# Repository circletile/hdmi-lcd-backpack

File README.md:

# hdmi-lcd-backpack
An HDMI signal converter backpack PCB

A circuit I designed for my electrical/computer engineering senior design project. Takes up to 1080p HDMI video signals, feeds them to a TI TFP401A signal converter, and directly drives an attached LCD. Also provides capacitive touch sensing, backlight control, and DDC data.

A few months later a similar product appeared for sale on Adafruit (#2219). Much easier to just buy theirs than to try to hand solder the TFP401A under a microscope like I did...

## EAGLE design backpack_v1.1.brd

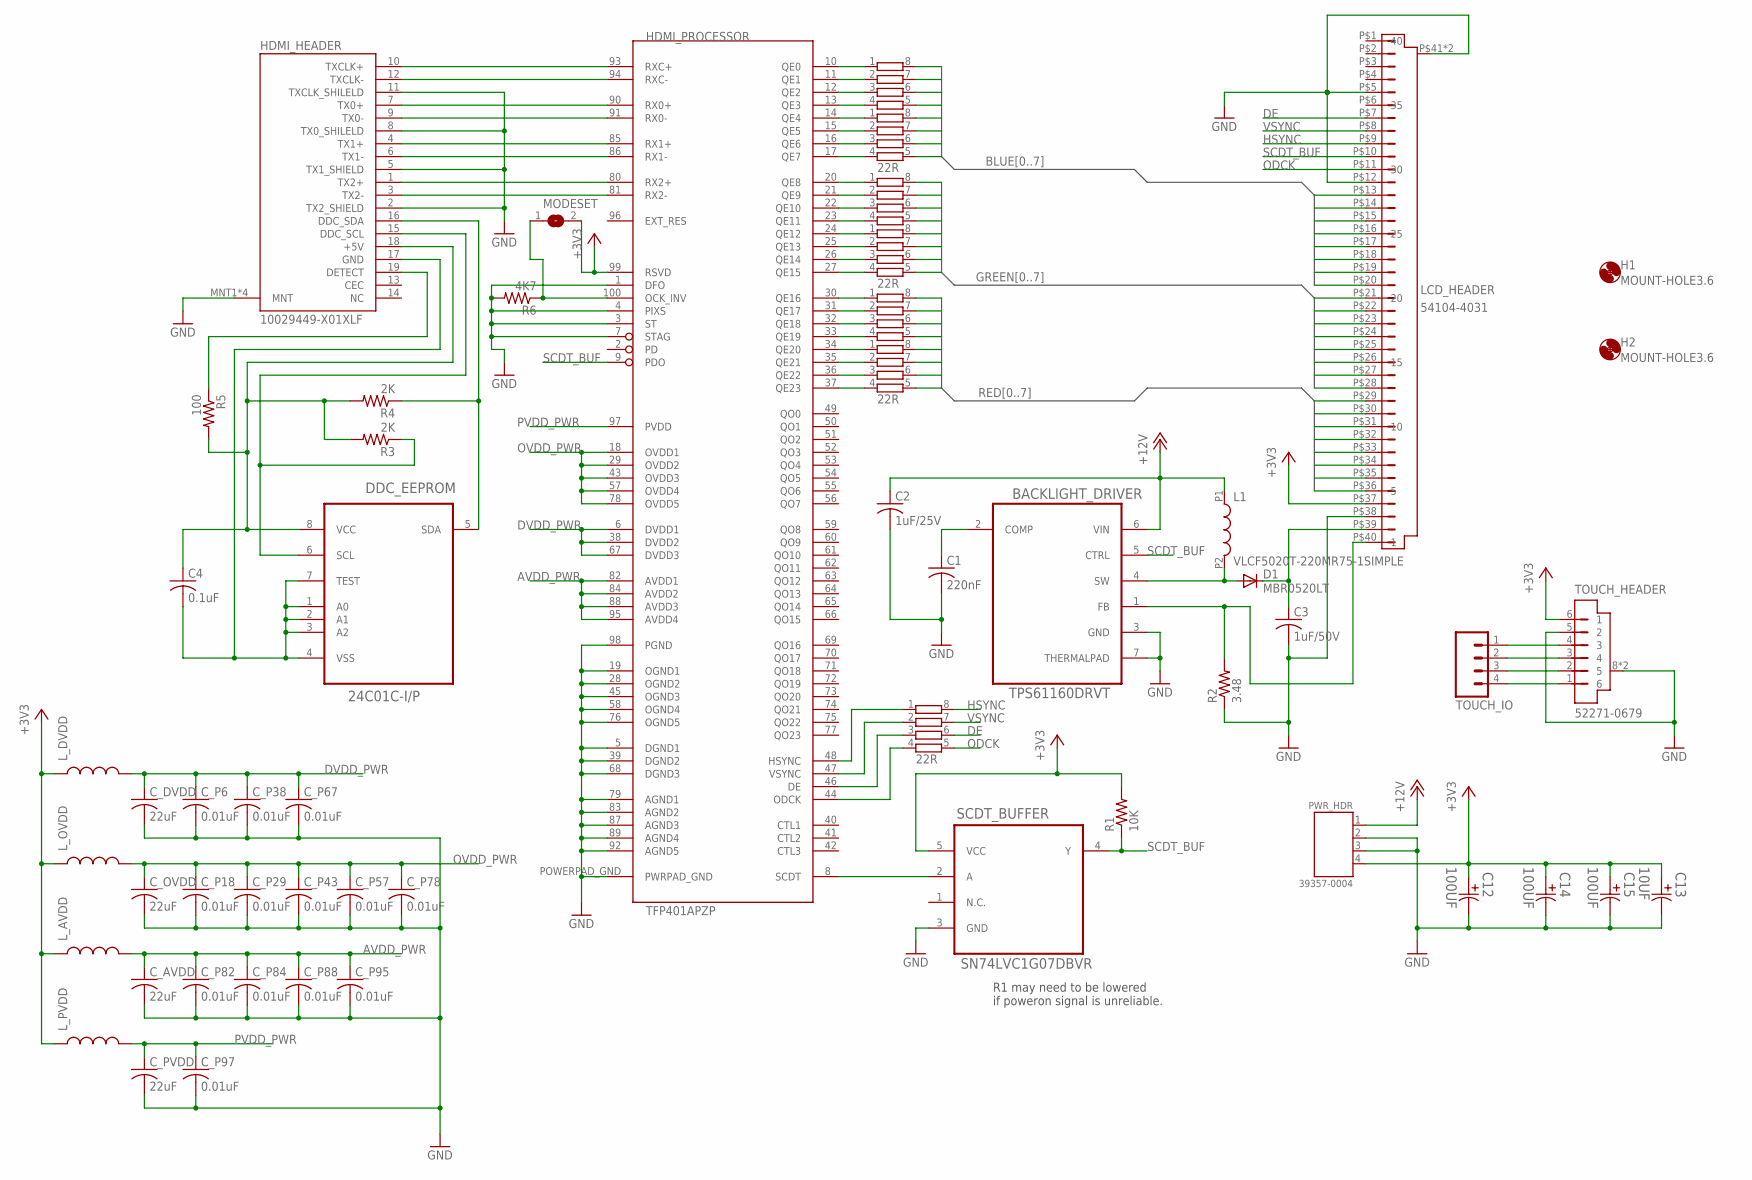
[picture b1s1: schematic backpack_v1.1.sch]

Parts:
BACKLIGHT_DRIVER: TPS61160DRVT; SON65P210X210X80-7N
C1: 220nF; C0805
C2: 1uF/25V; C0603
C3: 1uF/50V; C0805
C4: 0.1uF; C0603
C12, C14, C15: 100UF; CAPPR350-800X1150
C13: 10UF; CAPPR150-400X700
C_AVDD: 22uF; C0603
C_DVDD: 22uF; C0603
C_OVDD: 22uF; C0603
C_P6, C_P18, C_P29, C_P38, C_P43, C_P57, C_P67, C_P78, C_P82, C_P84, C_P88, C_P95, C_P97: 0.01uF; C0603
C_PVDD: 22uF; C0603
D1: MBR0520LT; SOD123
DDC_EEPROM: 24C01C-I/P; DIP254P762X533-8
H1, H2: MOUNT-HOLE3.6; 3,6
HDMI_HEADER: 10029449-X01XLF; 10029449
HDMI_PROCESSOR: TFP401APZP; 100-TQFP(PZP)
L1: VLCF5020T-220MR75-1SIMPLE; VLCF5020-1_SIMPLE
LCD_HEADER: 54104-4031
L_AVDD: INDUCTOR0603; 0603
L_DVDD: INDUCTOR0603; 0603
L_OVDD: INDUCTOR0603; 0603
L_PVDD: INDUCTOR0603; 0603
MODESET: SJ
PWR_HDR: 39357-0004
R1: 10K; R0805
R2: 3.48; R0805
R3, R4: 2K; R0805
R5: 100; R0805
R6: 4K7; R0805
RN1, RN2, RN3, RN4, RN5, RN6, RN7: 22R; CAY16
SCDT_BUFFER: SN74LVC1G07DBVR; SOT95P280X145-5N
TOUCH_HEADER: 52271-0679
TOUCH_IO: M04POLAR; MOLEX-1X4

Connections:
+3V3: C12.1, C13.1, C14.1, C15.1, HDMI_PROCESSOR.99 (RSVD), LCD_HEADER.P$37 (4), L_AVDD.1, L_DVDD.1, L_OVDD.1, L_PVDD.1, MODESET.2, PWR_HDR.4, R1.2, SCDT_BUFFER.5 (VCC), TOUCH_HEADER.6 (1)
+5V: C4.1, DDC_EEPROM.8 (VCC), HDMI_HEADER.18 (+5V), R3.2, R4.2, R5.2
+12V: BACKLIGHT_DRIVER.6 (VIN), C2.1, L1.P1, PWR_HDR.1
AVDD_PWR: C_AVDD.1, C_P82.1, C_P84.1, C_P88.1, C_P95.1, HDMI_PROCESSOR.82 (AVDD1), HDMI_PROCESSOR.84 (AVDD2), HDMI_PROCESSOR.88 (AVDD3), HDMI_PROCESSOR.95 (AVDD4), L_AVDD.2
BLUE0: LCD_HEADER.P$20 (21), RN1.8 (2)
BLUE1: LCD_HEADER.P$19 (22), RN1.7 (2)
BLUE2: LCD_HEADER.P$18 (23), RN1.6 (2)
BLUE3: LCD_HEADER.P$17 (24), RN1.5 (2)
BLUE4: LCD_HEADER.P$16 (25), RN2.8 (2)
BLUE5: LCD_HEADER.P$15 (26), RN2.7 (2)
BLUE6: LCD_HEADER.P$14 (27), RN2.6 (2)
BLUE7: LCD_HEADER.P$13 (28), RN2.5 (2)
DDC_SCL: DDC_EEPROM.6 (SCL), HDMI_HEADER.15 (DDC_SCL), R3.1
DDC_SDA: DDC_EEPROM.5 (SDA), HDMI_HEADER.16 (DDC_SDA), R4.1
DE: LCD_HEADER.P$7 (34), RN7.6 (2)
DVDD_PWR: C_DVDD.1, C_P6.1, C_P38.1, C_P67.1, HDMI_PROCESSOR.6 (DVDD1), HDMI_PROCESSOR.38 (DVDD2), HDMI_PROCESSOR.67 (DVDD3), L_DVDD.2
GND: BACKLIGHT_DRIVER.3 (GND), BACKLIGHT_DRIVER.7 (THERMALPAD), C1.2, C2.2, C3.2, C12.2, C13.2, C14.2, C15.2, C_AVDD.2, C_DVDD.2, C_OVDD.2, C_P6.2, C_P18.2, C_P29.2, C_P38.2, C_P43.2, C_P57.2, C_P67.2, C_P78.2, C_P82.2, C_P84.2, C_P88.2, C_P95.2, C_P97.2, C_PVDD.2, HDMI_HEADER.2 (TX2_SHIELD), HDMI_HEADER.5 (TX1_SHIELD), HDMI_HEADER.8 (TX0_SHILELD), HDMI_HEADER.11 (TXCLK_SHILELD), HDMI_HEADER.MNT1 (MNT), HDMI_HEADER.MNT2 (MNT), HDMI_HEADER.MNT3 (MNT), HDMI_HEADER.MNT4 (MNT), HDMI_PROCESSOR.1 (DFO), HDMI_PROCESSOR.3 (ST), HDMI_PROCESSOR.4 (PIXS), HDMI_PROCESSOR.5 (DGND1), HDMI_PROCESSOR.7 (STAG), HDMI_PROCESSOR.19 (OGND1), HDMI_PROCESSOR.28 (OGND2), HDMI_PROCESSOR.39 (DGND2), HDMI_PROCESSOR.45 (OGND3), HDMI_PROCESSOR.58 (OGND4), HDMI_PROCESSOR.68 (DGND3), HDMI_PROCESSOR.76 (OGND5), HDMI_PROCESSOR.79 (AGND1), HDMI_PROCESSOR.83 (AGND2), HDMI_PROCESSOR.87 (AGND3), HDMI_PROCESSOR.89 (AGND4), HDMI_PROCESSOR.92 (AGND5), HDMI_PROCESSOR.98 (PGND), HDMI_PROCESSOR.POWERPAD_GND (PWRPAD_GND), LCD_HEADER.P$5 (36), LCD_HEADER.P$12 (29), LCD_HEADER.P$38 (3), LCD_HEADER.P$41 (GND), LCD_HEADER.P$42 (GND), PWR_HDR.2, PWR_HDR.3, R2.1, R6.2, SCDT_BUFFER.3 (GND), TOUCH_HEADER.5 (2), TOUCH_HEADER.8 (GND), TOUCH_HEADER.9 (GND)
GREEN0: LCD_HEADER.P$28 (13), RN3.8 (2)
GREEN1: LCD_HEADER.P$27 (14), RN3.7 (2)
GREEN2: LCD_HEADER.P$26 (15), RN3.6 (2)
GREEN3: LCD_HEADER.P$25 (16), RN3.5 (2)
GREEN4: LCD_HEADER.P$24 (17), RN4.8 (2)
GREEN5: LCD_HEADER.P$23 (18), RN4.7 (2)
GREEN6: LCD_HEADER.P$22 (19), RN4.6 (2)
GREEN7: LCD_HEADER.P$21 (20), RN4.5 (2)
HDMI_DETECT: HDMI_HEADER.19 (DETECT), R5.1
HDMI_GND: C4.2, DDC_EEPROM.1 (A0), DDC_EEPROM.2 (A1), DDC_EEPROM.3 (A2), DDC_EEPROM.4 (VSS), DDC_EEPROM.7 (TEST), HDMI_HEADER.17 (GND)
HSYNC: LCD_HEADER.P$9 (32), RN7.8 (2)
unnamed: HDMI_PROCESSOR.10 (QE0), RN1.1
unnamed: HDMI_PROCESSOR.11 (QE1), RN1.2 (1)
unnamed: HDMI_PROCESSOR.12 (QE2), RN1.3 (1)
unnamed: HDMI_PROCESSOR.13 (QE3), RN1.4 (1)
unnamed: HDMI_PROCESSOR.14 (QE4), RN2.1
unnamed: HDMI_PROCESSOR.15 (QE5), RN2.2 (1)
unnamed: HDMI_PROCESSOR.16 (QE6), RN2.3 (1)
unnamed: HDMI_PROCESSOR.17 (QE7), RN2.4 (1)
unnamed: HDMI_PROCESSOR.20 (QE8), RN3.1
unnamed: HDMI_PROCESSOR.21 (QE9), RN3.2 (1)
unnamed: HDMI_PROCESSOR.22 (QE10), RN3.3 (1)
unnamed: HDMI_PROCESSOR.23 (QE11), RN3.4 (1)
unnamed: HDMI_PROCESSOR.24 (QE12), RN4.1
unnamed: HDMI_PROCESSOR.25 (QE13), RN4.2 (1)
unnamed: HDMI_PROCESSOR.26 (QE14), RN4.3 (1)
unnamed: HDMI_PROCESSOR.27 (QE15), RN4.4 (1)
unnamed: HDMI_PROCESSOR.30 (QE16), RN5.1
unnamed: HDMI_PROCESSOR.31 (QE17), RN5.2 (1)
unnamed: HDMI_PROCESSOR.32 (QE18), RN5.3 (1)
unnamed: HDMI_PROCESSOR.33 (QE19), RN5.4 (1)
unnamed: HDMI_PROCESSOR.34 (QE20), RN6.1
unnamed: HDMI_PROCESSOR.35 (QE21), RN6.2 (1)
unnamed: HDMI_PROCESSOR.36 (QE22), RN6.3 (1)
unnamed: HDMI_PROCESSOR.37 (QE23), RN6.4 (1)
unnamed: BACKLIGHT_DRIVER.4 (SW), D1.A, L1.P2
unnamed: BACKLIGHT_DRIVER.2 (COMP), C1.1
unnamed: BACKLIGHT_DRIVER.1 (FB), LCD_HEADER.P$40 (1), R2.2
unnamed: HDMI_PROCESSOR.44 (ODCK), RN7.4 (1)
unnamed: C3.1, D1.C, LCD_HEADER.P$39 (2)
unnamed: HDMI_PROCESSOR.46 (DE), RN7.3 (1)
unnamed: HDMI_PROCESSOR.47 (VSYNC), RN7.2 (1)
unnamed: HDMI_PROCESSOR.48 (HSYNC), RN7.1
unnamed: TOUCH_HEADER.4 (3), TOUCH_IO.1
unnamed: TOUCH_HEADER.3 (4), TOUCH_IO.2
unnamed: TOUCH_HEADER.2 (5), TOUCH_IO.3
unnamed: TOUCH_HEADER.1 (6), TOUCH_IO.4
OCK_INV: HDMI_PROCESSOR.100 (OCK_INV), MODESET.1, R6.1
ODCK: LCD_HEADER.P$11 (30), RN7.5 (2)
OVDD_PWR: C_OVDD.1, C_P18.1, C_P29.1, C_P43.1, C_P57.1, C_P78.1, HDMI_PROCESSOR.18 (OVDD1), HDMI_PROCESSOR.29 (OVDD2), HDMI_PROCESSOR.43 (OVDD3), HDMI_PROCESSOR.57 (OVDD4), HDMI_PROCESSOR.78 (OVDD5), L_OVDD.2
PVDD_PWR: C_P97.1, C_PVDD.1, HDMI_PROCESSOR.97 (PVDD), L_PVDD.2
RED0: LCD_HEADER.P$36 (5), RN5.8 (2)
RED1: LCD_HEADER.P$35 (6), RN5.7 (2)
RED2: LCD_HEADER.P$34 (7), RN5.6 (2)
RED3: LCD_HEADER.P$33 (8), RN5.5 (2)
RED4: LCD_HEADER.P$32 (9), RN6.8 (2)
RED5: LCD_HEADER.P$31 (10), RN6.7 (2)
RED6: LCD_HEADER.P$30 (11), RN6.6 (2)
RED7: LCD_HEADER.P$29 (12), RN6.5 (2)
SCDT: HDMI_PROCESSOR.8 (SCDT), SCDT_BUFFER.2 (A)
SCDT_BUF: BACKLIGHT_DRIVER.5 (CTRL), HDMI_PROCESSOR.9 (PDO), LCD_HEADER.P$10 (31), R1.1, SCDT_BUFFER.4 (Y)
TX0_N: HDMI_HEADER.9 (TX0-), HDMI_PROCESSOR.91 (RX0-)
TX0_P: HDMI_HEADER.7 (TX0+), HDMI_PROCESSOR.90 (RX0+)
TX1_N: HDMI_HEADER.6 (TX1-), HDMI_PROCESSOR.86 (RX1-)
TX1_P: HDMI_HEADER.4 (TX1+), HDMI_PROCESSOR.85 (RX1+)
TX2_N: HDMI_HEADER.3 (TX2-), HDMI_PROCESSOR.81 (RX2-)
TX2_P: HDMI_HEADER.1 (TX2+), HDMI_PROCESSOR.80 (RX2+)
TXCLK_N: HDMI_HEADER.12 (TXCLK-), HDMI_PROCESSOR.94 (RXC-)
TXCLK_P: HDMI_HEADER.10 (TXCLK+), HDMI_PROCESSOR.93 (RXC+)
VSYNC: LCD_HEADER.P$8 (33), RN7.7 (2)

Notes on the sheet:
R1 may need to be lowered if poweron signal is unreliable.

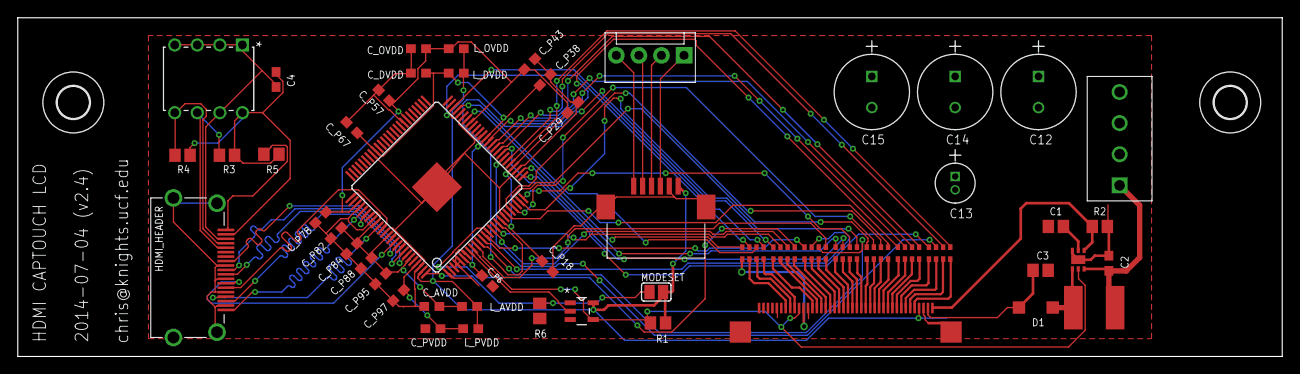
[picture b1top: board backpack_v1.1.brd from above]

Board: 2 copper layers, 142.2 x 38.1 mm, 56 parts (0 on the bottom side), 87 nets.

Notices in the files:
parts and their libraries:
SparkFun-Passives: Licensing: CC v3.0 Share-Alike You are welcome to use this library for commercial purposes.
